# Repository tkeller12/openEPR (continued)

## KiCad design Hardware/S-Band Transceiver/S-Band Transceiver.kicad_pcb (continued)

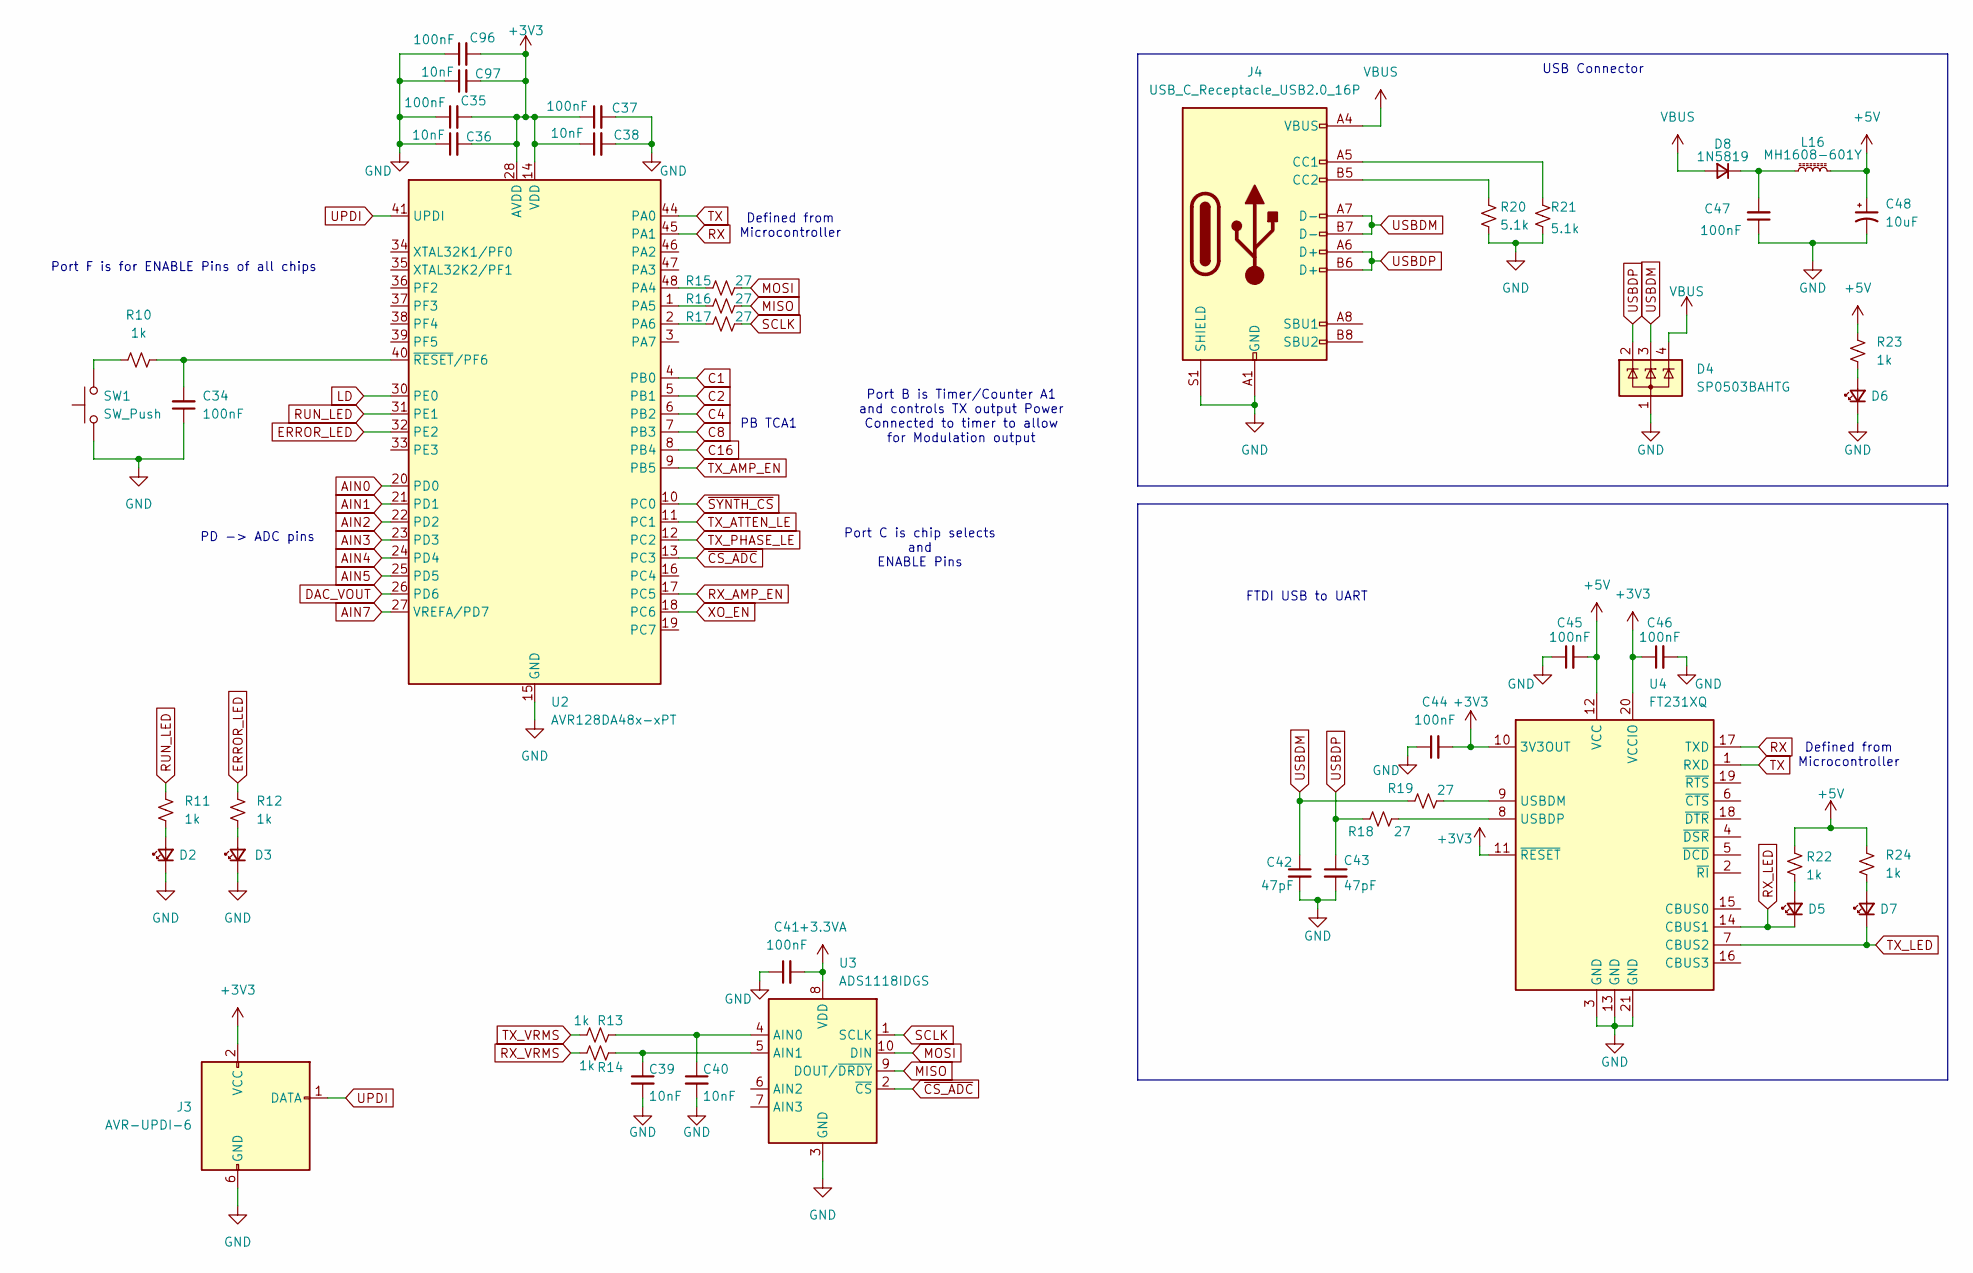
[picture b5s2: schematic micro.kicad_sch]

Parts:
C34, C35, C37, C41, C44, C45, C46, C47, C96: 100nF; C_0402_1005Metric
C36, C38, C39, C40, C97: 10nF; C_0402_1005Metric
C42, C43: 47pF; C_0402_1005Metric
C48: 10uF; CP_EIA-3216-18_Kemet-A
D2, D5, D6, D7: 150080VS75000; LED_0805_2012Metric
D3: 150080SS75000; LED_0805_2012Metric
D4: SP0503BAHTG; SOT-143; Digikey F2715CT-ND
D8: 1N5819; D_SOD-123
J3: AVR-UPDI-6; IDC-Header_2x03_P2.54mm_Vertical
J4: USB_C_Receptacle_USB2.0_16P; USB_C_Receptacle_GCT_USB4085; Digikey 2073-USB4085-GF-ACT-ND
L16: MH1608-601Y; L_0603_1608Metric
R10, R11, R12, R13, R14, R22, R23, R24: 1k; R_0603_1608Metric
R15, R16, R17, R18, R19: 27; R_0603_1608Metric
R20, R21: 5.1k; R_0603_1608Metric
SW1: SW_Push; SW_SPST_B3SL-1002P
U2: AVR128DA48x-xPT; TQFP-48_7x7mm_P0.5mm; Digikey 150-AVR128DA48-I/PT-ND
U3: ADS1118IDGS; MSOP-10_3x3mm_P0.5mm; Digikey 296-38850-1-ND
U4: FT231XQ; QFN-20-1EP_4x4mm_P0.5mm_EP2.5x2.5mm; Digikey 768-1128-1-ND

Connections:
+3.3VA: C41.2, U3.8 (VDD); also elsewhere on the board
+3V3: C35.2, C36.2, C37.1, C38.1, C44.2, C46.1, C96.2, C97.2, J3.2 (VCC), U2.14 (VDD), U2.28 (AVDD), U2.42 (VDD), U4.10 (3V3OUT), U4.11 (~RESET), U4.20 (VCCIO)
+5V: C45.2, C48.1, L16.2, R22.1, R23.1, R24.1, U4.12 (VCC); also elsewhere on the board
AIN0: U2.20 (PD0)
AIN1: U2.21 (PD1)
AIN2: U2.22 (PD2)
AIN3: U2.23 (PD3)
AIN4: U2.24 (PD4)
AIN5: U2.25 (PD5)
AIN7: U2.27 (VREFA/PD7)
C1: U2.4 (PB0); also elsewhere on the board
C2: U2.5 (PB1); also elsewhere on the board
C4: U2.6 (PB2); also elsewhere on the board
C8: U2.7 (PB3); also elsewhere on the board
C16: U2.8 (PB4); also elsewhere on the board
DAC_VOUT: U2.26 (PD6)
ERROR_LED: R12.1, U2.32 (PE2)
GND: C34.1, C35.1, C36.1, C37.2, C38.2, C39.2, C40.2, C41.1, C42.2, C43.2, C44.1, C45.1, C46.2, C47.1, C48.2, C96.1, C97.1, D2.1 (K), D3.1 (K), D4.1 (A), D6.1 (K), J3.6 (GND), J4.A1 (GND), J4.A12 (GND), J4.B1 (GND), J4.B12 (GND), J4.S1 (SHIELD), R20.2, R21.2, SW1.1, U2.15 (GND), U2.29 (GND), U2.43 (GND), U3.3 (GND), U4.3 (GND), U4.13 (GND), U4.21 (GND); also elsewhere on the board
LD: U2.30 (PE0); also elsewhere on the board
MISO: R16.2, U3.9 (DOUT/~DRDY)
MOSI: R15.2, U3.10 (DIN); also elsewhere on the board
unnamed: D2.2 (A), R11.2
unnamed: D3.2 (A), R12.2
unnamed: D5.2 (A), R22.2
unnamed: D6.2 (A), R23.2
unnamed: D7.2 (A), R24.2
unnamed: C47.2, D8.1 (K), L16.1
unnamed: J4.A5 (CC1), R21.1
unnamed: J4.B5 (CC2), R20.1
unnamed: R10.1, SW1.2
unnamed: R15.1, U2.48 (PA4)
unnamed: R16.1, U2.1 (PA5)
unnamed: R17.1, U2.2 (PA6)
unnamed: C34.2, R10.2, U2.40 (~RESET/PF6)
unnamed: C40.1, R13.2, U3.4 (AIN0)
unnamed: C39.1, R14.2, U3.5 (AIN1)
unnamed: R19.2, U4.9 (USBDM)
unnamed: R18.2, U4.8 (USBDP)
RUN_LED: R11.1, U2.31 (PE1)
RX: U2.45 (PA1), U4.17 (TXD)
RX_AMP_EN: U2.17 (PC5); also elsewhere on the board
RX_LED: D5.1 (K), U4.14 (CBUS1)
RX_VRMS: R14.1; also elsewhere on the board
SCLK: R17.2, U3.1 (SCLK); also elsewhere on the board
TX: U2.44 (PA0), U4.1 (RXD)
TX_AMP_EN: U2.9 (PB5); also elsewhere on the board
TX_ATTEN_LE: U2.11 (PC1); also elsewhere on the board
TX_LED: D7.1 (K), U4.7 (CBUS2)
TX_PHASE_LE: U2.12 (PC2); also elsewhere on the board
TX_VRMS: R13.1; also elsewhere on the board
UPDI: J3.1 (DATA), U2.41 (UPDI)
USBDM: C42.1, D4.3 (K), J4.A7 (D-), J4.B7 (D-), R19.1
USBDP: C43.1, D4.2 (K), J4.A6 (D+), J4.B6 (D+), R18.1
VBUS: D4.4 (K), D8.2 (A), J4.A4 (VBUS), J4.A9 (VBUS), J4.B4 (VBUS), J4.B9 (VBUS)
XO_EN: U2.18 (PC6); also elsewhere on the board
~CS_ADC: U2.13 (PC3), U3.2 (~CS)
~SYNTH_CS: U2.10 (PC0); also elsewhere on the board

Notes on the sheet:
Defined from Microcontroller
Port F is for ENABLE Pins of all chips
Port C is chip selects and ENABLE Pins
PB TCA1
Port B is Timer/Counter A1 and controls TX output Power Connected to timer to allow for Modulation output
PD -> ADC pins
FTDI USB to UART
USB Connector

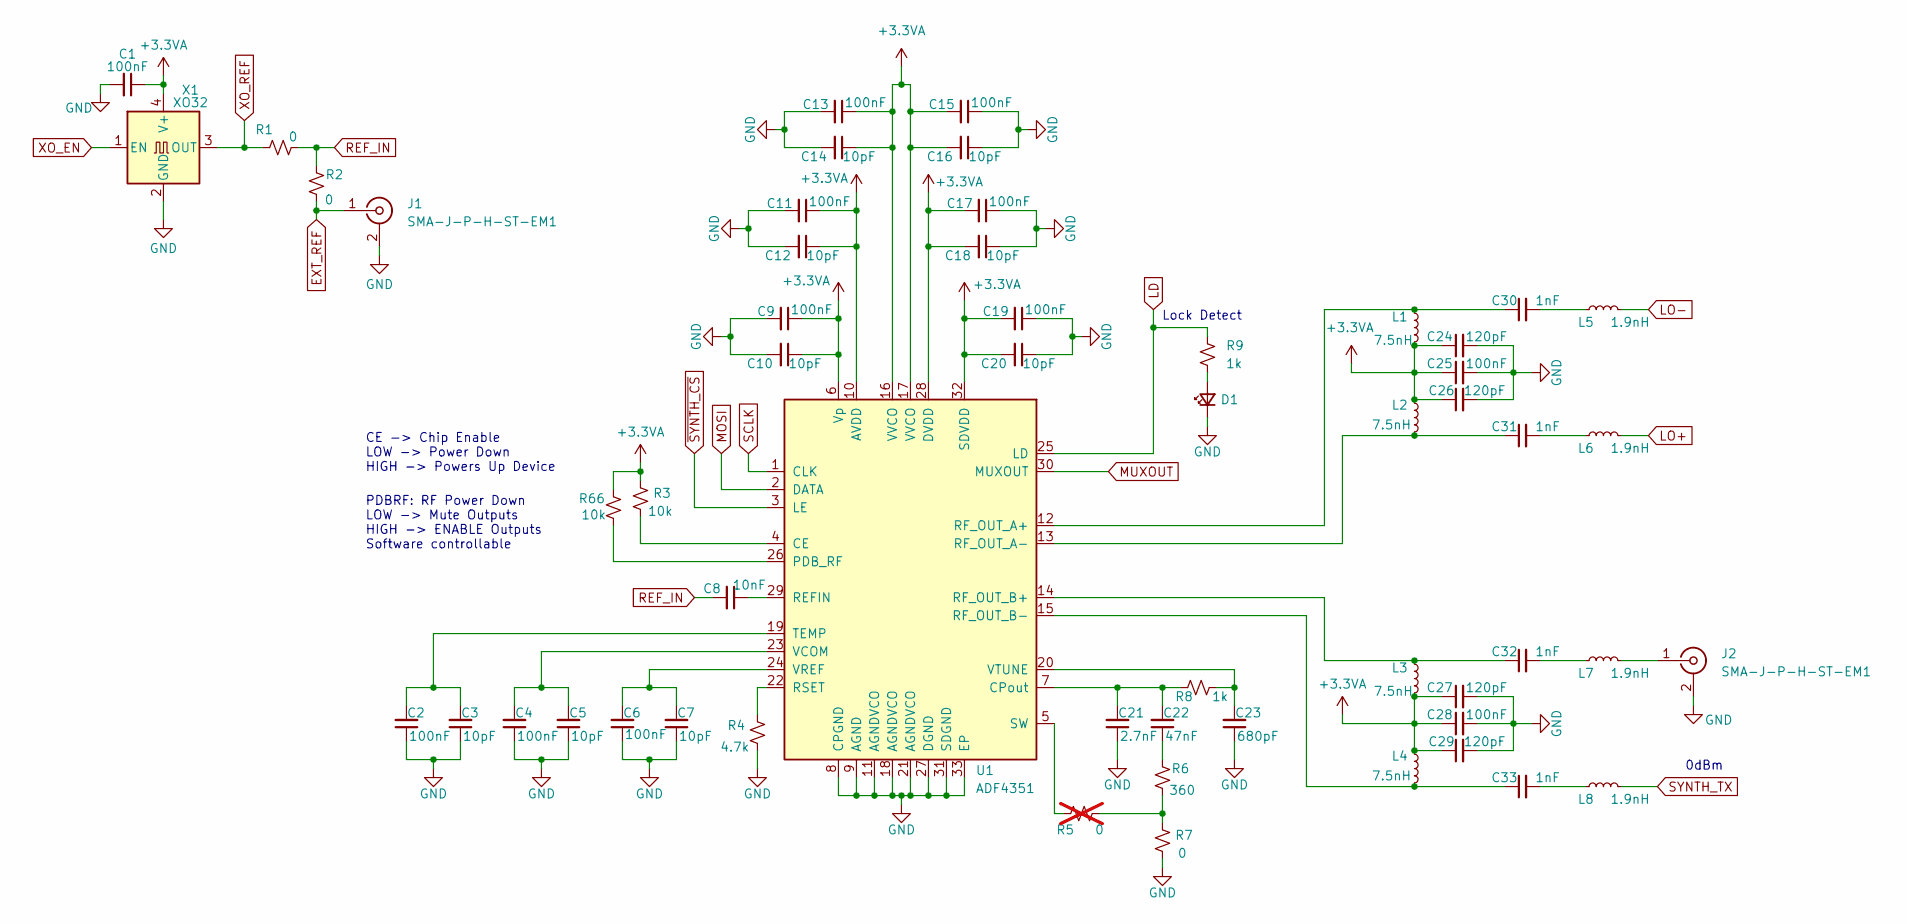
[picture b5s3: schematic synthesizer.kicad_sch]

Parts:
C1, C2, C4, C6, C9, C11, C13, C15, C17, C19, C25, C28: 100nF; C_0402_1005Metric
C3, C5, C7, C10, C12, C14, C16, C18, C20: 10pF; C_0402_1005Metric
C8: 10nF; C_0402_1005Metric
C21: 2.7nF; C_0603_1608Metric
C22: 47nF; C_0603_1608Metric
C23: 680pF; C_0603_1608Metric
C24, C26, C27, C29: 120pF; C_0402_1005Metric
C30, C31, C32, C33: 1nF; C_0402_1005Metric
D1: 150080VS75000; LED_0805_2012Metric
J1, J2: SMA-J-P-H-ST-EM1; SMA_Samtec_SMA-J-P-X-ST-EM1_EdgeMount; Digikey SAM8857-ND
L1, L2, L3, L4: 7.5nH; L_0402_1005Metric
L5, L6, L7, L8: 1.9nH; L_0402_1005Metric
R1, R2, R7: 0; R_0603_1608Metric
R3, R66: 10k; R_0603_1608Metric
R4: 4.7k; R_0603_1608Metric
R5: 0; R_0603_1608Metric; not fitted
R6: 360; R_0603_1608Metric
R8, R9: 1k; R_0603_1608Metric
U1: ADF4351; LFCSP-32-1EP_5x5mm_P0.5mm_EP3.25x3.25mm; Digikey 505-ADF4351BCPZ-RL7CT-ND
X1: XO32; Oscillator_SMD_EuroQuartz_XO32-4Pin_3.2x2.5mm

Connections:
+3.3VA: C1.1, C9.1, C10.1, C11.1, C12.1, C13.1, C14.1, C15.2, C16.2, C17.2, C18.2, C19.2, C20.2, C24.1, C25.1, C26.1, C27.1, C28.1, C29.1, L1.2, L2.1, L3.2, L4.1, R3.2, R66.1, U1.6 (Vp), U1.10 (AVDD), U1.16 (VVCO), U1.17 (VVCO), U1.28 (DVDD), U1.32 (SDVDD), X1.4 (V+); also elsewhere on the board
EXT_REF: J1.1 (In), R2.1
GND: C1.2, C2.1, C3.1, C4.1, C5.1, C6.1, C7.1, C9.2, C10.2, C11.2, C12.2, C13.2, C14.2, C15.1, C16.1, C17.1, C18.1, C19.1, C20.1, C21.1, C23.1, C24.2, C25.2, C26.2, C27.2, C28.2, C29.2, D1.1 (K), J1.2 (Ext), J2.2 (Ext), R4.2, R7.1, U1.8 (CPGND), U1.9 (AGND), U1.11 (AGNDVCO), U1.18 (AGNDVCO), U1.21 (AGNDVCO), U1.27 (DGND), U1.31 (SDGND), U1.33 (EP), X1.2 (GND); also elsewhere on the board
LD: R9.1, U1.25 (LD); also elsewhere on the board
LO+: L6.2; also elsewhere on the board
LO-: L5.2; also elsewhere on the board
MOSI: U1.2 (DATA); also elsewhere on the board
MUXOUT: U1.30 (MUXOUT)
unnamed: C22.1, R6.2
unnamed: C30.2, L5.1
unnamed: C31.2, L6.1
unnamed: C32.2, L7.1
unnamed: C33.2, L8.1
unnamed: D1.2 (A), R9.2
unnamed: J2.1 (In), L7.2
unnamed: R5.1, R6.1, R7.2
unnamed: R3.1, U1.4 (CE)
unnamed: C21.2, C22.2, R8.1, U1.7 (CPout)
unnamed: R66.2, U1.26 (PDB_RF)
unnamed: C8.1, U1.29 (REFIN)
unnamed: C30.1, L1.1, U1.12 (RF_OUT_A+)
unnamed: C31.1, L2.2, U1.13 (RF_OUT_A-)
unnamed: C32.1, L3.1, U1.14 (RF_OUT_B+)
unnamed: C33.1, L4.2, U1.15 (RF_OUT_B-)
unnamed: R4.1, U1.22 (RSET)
unnamed: R5.2, U1.5 (SW)
unnamed: C2.2, C3.2, U1.19 (TEMP)
unnamed: C4.2, C5.2, U1.23 (VCOM)
unnamed: C6.2, C7.2, U1.24 (VREF)
unnamed: C23.2, R8.2, U1.20 (VTUNE)
REF_IN: C8.2, R1.2, R2.2
SCLK: U1.1 (CLK); also elsewhere on the board
SYNTH_TX: L8.2; also elsewhere on the board
XO_EN: X1.1 (EN); also elsewhere on the board
XO_REF: R1.1, X1.3 (OUT)
~SYNTH_CS: U1.3 (LE); also elsewhere on the board

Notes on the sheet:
Lock Detect
0dBm
PDBRF: RF Power Down LOW -> Mute Outputs HIGH -> ENABLE Outputs Software controllable
CE -> Chip Enable LOW -> Power Down HIGH -> Powers Up Device

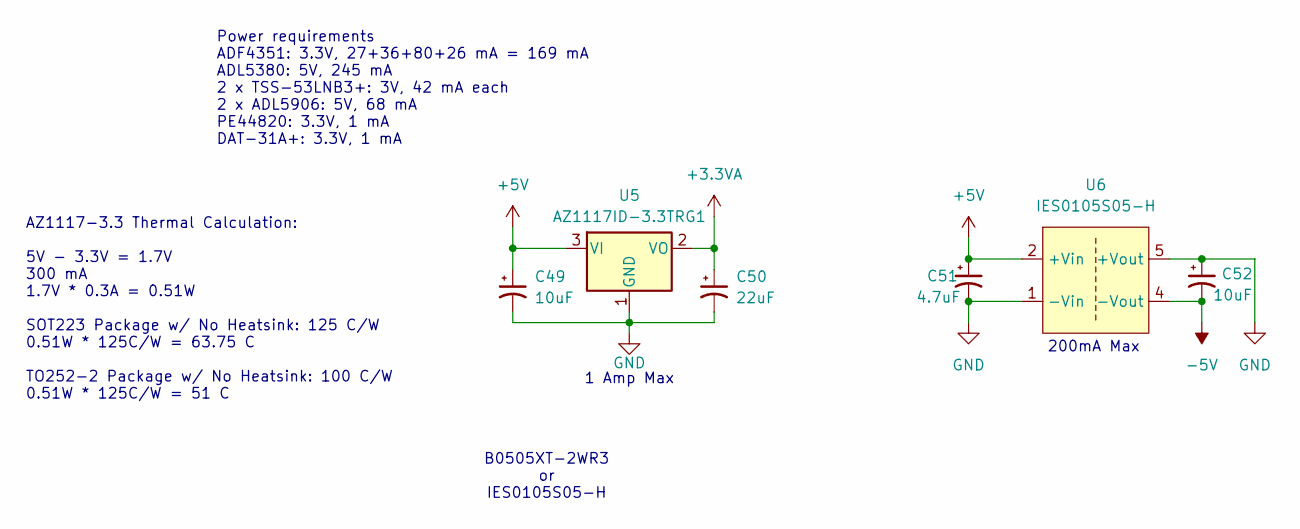
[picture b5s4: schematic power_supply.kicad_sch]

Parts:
C49, C52: 10uF
C50: 22uF
C51: 4.7uF
U5: AZ1117ID-3.3TRG1; TO-252-2; Digikey AZ1117ID-3.3TRG1-ND
U6: IES0105S05-H; Digikey 1470-IES0105S05-H-ND

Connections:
+3.3VA: C50.1, U5.2 (VO); also elsewhere on the board
+5V: C49.1, C51.1, U5.3 (VI), U6.2 (+Vin); also elsewhere on the board
-5V: C52.2, U6.4 (-Vout); also elsewhere on the board
GND: C49.2, C50.2, C51.2, C52.1, U5.1 (GND), U6.1 (-Vin), U6.5 (+Vout); also elsewhere on the board

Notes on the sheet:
B0505XT-2WR3 or IES0105S05-H
AZ1117-3.3 Thermal Calculation: 5V - 3.3V = 1.7V 300 mA 1.7V * 0.3A = 0.51W SOT223 Package w/ No Heatsink: 125 C/W 0.51W * 125C/W = 63.75 C TO252-2 Package w/ No Heatsink: 100 C/W 0.51W * 125C/W = 51 C
200mA Max
Power requirements ADF4351: 3.3V, 27+36+80+26 mA = 169 mA ADL5380: 5V, 245 mA 2 x TSS-53LNB3+: 3V, 42 mA each 2 x ADL5906: 5V, 68 mA PE44820: 3.3V, 1 mA DAT-31A+: 3.3V, 1 mA
1 Amp Max

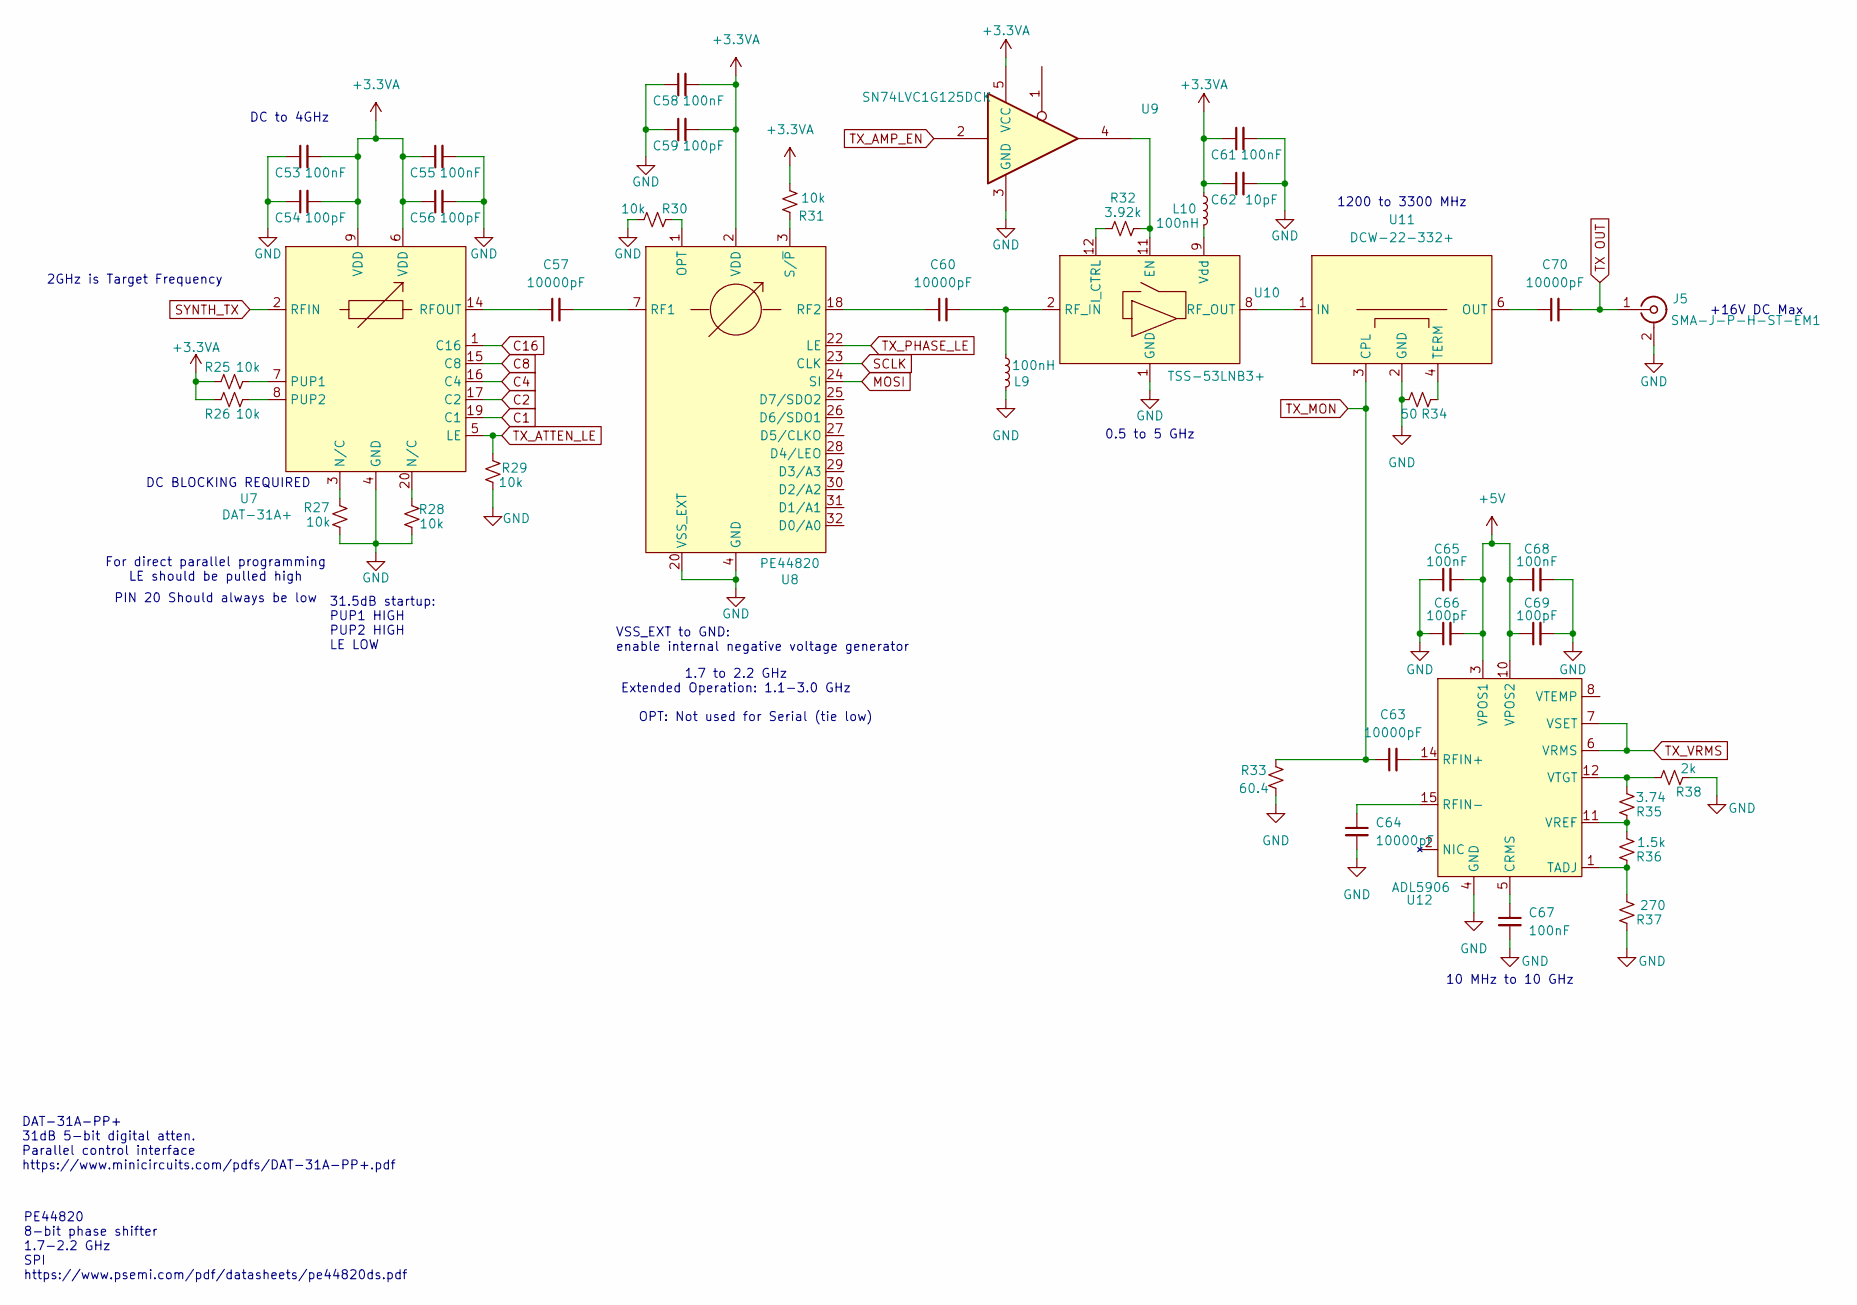
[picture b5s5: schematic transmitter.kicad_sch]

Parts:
C53, C55, C58, C61, C65, C67, C68: 100nF; C_0402_1005Metric
C54, C56, C59, C66, C69: 100pF; C_0402_1005Metric
C57, C60, C63, C64, C70: 10000pF; C_0402_1005Metric; Digikey 1284-1540-1-ND
C62: 10pF; C_0402_1005Metric
J5: SMA-J-P-H-ST-EM1; SMA_Samtec_SMA-J-P-X-ST-EM1_EdgeMount; Digikey SAM8857-ND
L9, L10: 100nH; L_0402_1005Metric
R25, R26, R27, R28, R29, R30, R31: 10k; R_0603_1608Metric
R32: 3.92k; R_0603_1608Metric
R33: 60.4; R_0603_1608Metric
R34: 50; R_0603_1608Metric
R35: 3.74; R_0603_1608Metric
R36: 1.5k; R_0603_1608Metric
R37: 270; R_0603_1608Metric
R38: 2k; R_0603_1608Metric
U7: DAT-31A+; QFN-20-1EP_4x4mm_P0.5mm_EP2.5x2.5mm; Digikey 3157-DAT-31A-PP+CT-ND
U8: PE44820; QFN-32-1EP_5x5mm_P0.5mm_EP3.6x3.6mm; Digikey 1046-1144-1-ND
U9: SN74LVC1G125DCK; SOT-23-5; Digikey 296-11604-1-ND
U10: TSS-53LNB3+; DQ1225; Digikey 3157-TSS-53LNB3+CT-ND
U11: DCW-22-332+; JC0603C; Digikey 3157-DCW-22-332+CT-ND
U12: ADL5906; QFN-16-1EP_4x4mm_P0.65mm_EP2.1x2.1mm_ThermalVias; Digikey 505-ADL5906ACPZN-R7CT-ND

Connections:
+3.3VA: C53.2, C54.2, C55.1, C56.1, C58.2, C59.2, C61.1, C62.1, L10.1, R25.2, R26.2, R31.1, U7.6 (VDD), U7.9 (VDD), U8.2 (VDD), U9.5 (VCC); also elsewhere on the board
+5V: C65.2, C66.2, C68.1, C69.1, U12.3 (VPOS1), U12.10 (VPOS2); also elsewhere on the board
C1: U7.19 (C1); also elsewhere on the board
C2: U7.17 (C2); also elsewhere on the board
C4: U7.16 (C4); also elsewhere on the board
C8: U7.15 (C8); also elsewhere on the board
C16: U7.1 (C16); also elsewhere on the board
GND: C53.1, C54.1, C55.2, C56.2, C58.1, C59.1, C61.2, C62.2, C64.2, C65.1, C66.1, C67.2, C68.2, C69.2, J5.2 (Ext), L9.2, R27.1, R28.1, R29.1, R30.1, R33.2, R34.1, R37.1, R38.2, U7.4 (GND), U7.10 (GND), U7.11 (GND), U7.12 (GND), U7.13 (GND), U7.18 (GND), U7.21 (GND), U8.4 (GND), U8.5 (GND), U8.6 (GND), U8.8 (GND), U8.9 (GND), U8.10 (GND), U8.11 (GND), U8.12 (GND), U8.13 (GND), U8.14 (GND), U8.15 (GND), U8.16 (GND), U8.17 (GND), U8.19 (GND), U8.20 (VSS_EXT), U8.21 (GND), U8.33 (PAD), U9.3 (GND), U10.1 (GND), U10.3 (GND), U10.4 (GND), U10.5 (GND), U10.6 (GND), U10.7 (GND), U10.10 (GND), U10.13 (GND), U11.2 (GND), U11.5 (GND), U12.4 (GND), U12.9 (GND), U12.17 (GND); also elsewhere on the board
MOSI: U8.24 (SI); also elsewhere on the board
unnamed: R27.2, U7.3 (N/C)
unnamed: R28.2, U7.20 (N/C)
unnamed: R25.1, U7.7 (PUP1)
unnamed: R26.1, U7.8 (PUP2)
unnamed: C57.1, U7.14 (RFOUT)
unnamed: R30.2, U8.1 (OPT)
unnamed: C57.2, U8.7 (RF1)
unnamed: C60.1, U8.18 (RF2)
unnamed: R31.2, U8.3 (S/~P)
unnamed: R32.2, U9.4, U10.11 (EN)
unnamed: R32.1, U10.12 (I_CTRL)
unnamed: C60.2, L9.1, U10.2 (RF_IN)
unnamed: U10.8 (RF_OUT), U11.1 (IN)
unnamed: L10.2, U10.9 (Vdd)
unnamed: C70.1, U11.6 (OUT)
unnamed: R34.2, U11.4 (TERM)
unnamed: C67.1, U12.5 (CRMS)
unnamed: C63.2, U12.14 (RFIN+)
unnamed: C64.1, U12.15 (RFIN-)
unnamed: R36.1, R37.2, U12.1 (TADJ)
unnamed: R35.1, R36.2, U12.11 (VREF)
unnamed: R35.2, R38.1, U12.12 (VTGT)
SCLK: U8.23 (CLK); also elsewhere on the board
SYNTH_TX: U7.2 (RFIN); also elsewhere on the board
TX OUT: C70.2, J5.1 (In)
TX_AMP_EN: U9.2; also elsewhere on the board
TX_ATTEN_LE: R29.2, U7.5 (LE); also elsewhere on the board
TX_MON: C63.1, R33.1, U11.3 (CPL)
TX_PHASE_LE: U8.22 (LE); also elsewhere on the board
TX_VRMS: U12.6 (VRMS), U12.7 (VSET); also elsewhere on the board

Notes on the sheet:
10 MHz to 10 GHz
0.5 to 5 GHz
+16V DC Max
DC to 4GHz
DC BLOCKING REQUIRED
PE44820 8-bit phase shifter 1.7-2.2 GHz SPI https://www.psemi.com/pdf/datasheets/pe44820ds.pdf
1.7 to 2.2 GHz Extended Operation: 1.1-3.0 GHz
OPT: Not used for Serial (tie low)
PIN 20 Should always be low
DAT-31A-PP+ 31dB 5-bit digital atten. Parallel control interface https://www.minicircuits.com/pdfs/DAT-31A-PP+.pdf
For direct parallel programming LE should be pulled high
1200 to 3300 MHz
31.5dB startup: PUP1 HIGH PUP2 HIGH LE LOW
2GHz is Target Frequency
VSS_EXT to GND: enable internal negative voltage generator

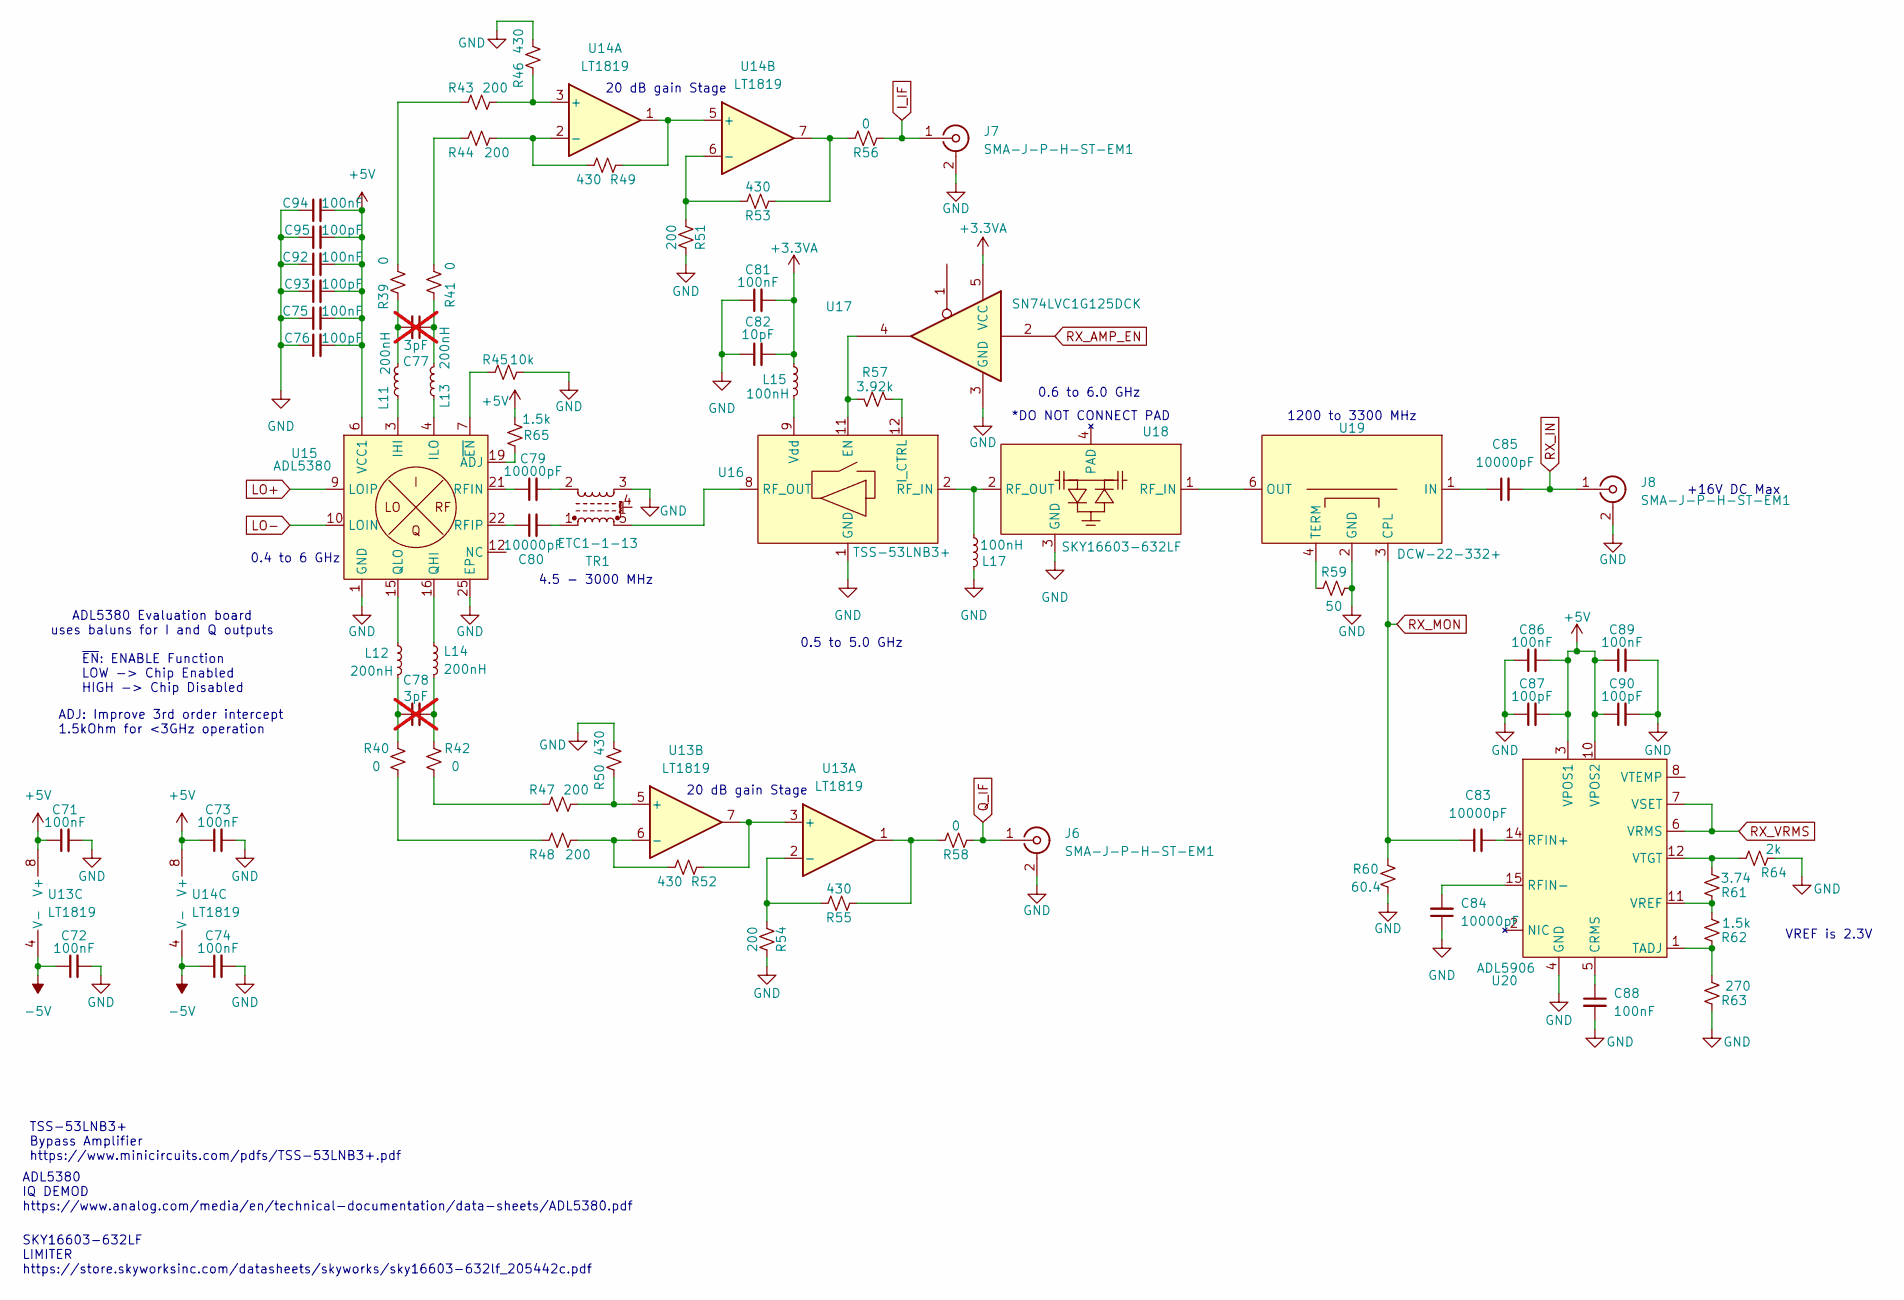
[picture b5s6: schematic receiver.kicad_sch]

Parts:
C71, C72, C73, C74, C75, C81, C86, C88, C89, C92, C94: 100nF; C_0402_1005Metric
C76, C87, C90, C93, C95: 100pF; C_0402_1005Metric
C77, C78: 3pF; C_0402_1005Metric; not fitted
C79, C80, C83, C84, C85: 10000pF; C_0402_1005Metric; Digikey 1284-1540-1-ND
C82: 10pF; C_0402_1005Metric
J6, J7, J8: SMA-J-P-H-ST-EM1; SMA_Samtec_SMA-J-P-X-ST-EM1_EdgeMount; Digikey SAM8857-ND
L11, L12, L13, L14: 200nH; L_0402_1005Metric
L15, L17: 100nH; L_0402_1005Metric
R39, R40, R41, R42, R56, R58: 0; R_0603_1608Metric
R43, R44, R47, R48, R51, R54: 200; R_0603_1608Metric
R45: 10k; R_0603_1608Metric
R46, R49, R50, R52, R53, R55: 430; R_0603_1608Metric
R57: 3.92k; R_0603_1608Metric
R59: 50; R_0603_1608Metric
R60: 60.4; R_0603_1608Metric
R61: 3.74; R_0603_1608Metric
R62, R65: 1.5k; R_0603_1608Metric
R63: 270; R_0603_1608Metric
R64: 2k; R_0603_1608Metric
TR1: ETC1-1-13; Transformer_MACOM_SM-22; Digikey 1465-1217-1-ND
U13, U14: LT1819; MSOP-8_3x3mm_P0.65mm; Digikey LT1819CS8#TRPBFCT-ND
U15: ADL5380; LFCSP-24-1EP_4x4mm_P0.5mm_EP2.3x2.3mm_ThermalVias; Digikey 505-ADL5380ACPZ-R7CT-ND
U16: TSS-53LNB3+; DQ1225; Digikey 3157-TSS-53LNB3+CT-ND
U17: SN74LVC1G125DCK; SOT-23-5; Digikey 296-11604-1-ND
U18: SKY16603-632LF; DFN-2-2.3x2.3; Digikey 863-SKY16603-632LFCT-ND
U19: DCW-22-332+; JC0603C; Digikey 3157-DCW-22-332+CT-ND
U20: ADL5906; QFN-16-1EP_4x4mm_P0.65mm_EP2.1x2.1mm_ThermalVias; Digikey 505-ADL5906ACPZN-R7CT-ND

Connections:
+3.3VA: C81.2, C82.2, L15.1, U17.5 (VCC); also elsewhere on the board
+5V: C71.1, C73.1, C75.2, C76.2, C86.2, C87.2, C89.1, C90.1, C92.2, C93.2, C94.2, C95.2, R65.1, U13.8 (V+), U14.8 (V+), U15.6 (VCC1), U15.13 (VCC2), U15.24 (VCC3), U20.3 (VPOS1), U20.10 (VPOS2); also elsewhere on the board
-5V: C72.1, C74.1, U13.4 (V-), U14.4 (V-); also elsewhere on the board
GND: C71.2, C72.2, C73.2, C74.2, C75.1, C76.1, C81.1, C82.1, C84.1, C86.1, C87.1, C88.2, C89.2, C90.2, C92.1, C93.1, C94.1, C95.1, J6.2 (Ext), J7.2 (Ext), J8.2 (Ext), L17.2, R45.1, R46.1, R50.1, R51.1, R54.1, R59.2, R60.2, R63.1, R64.2, TR1.3, U15.1 (GND), U15.2 (GND), U15.5 (GND), U15.8 (GND), U15.11 (GND), U15.14 (GND), U15.17 (GND), U15.18 (GND), U15.20 (GND), U15.23 (GND), U15.25 (EP), U16.1 (GND), U16.3 (GND), U16.4 (GND), U16.5 (GND), U16.6 (GND), U16.7 (GND), U16.10 (GND), U16.13 (GND), U17.3 (GND), U18.3 (GND), U19.2 (GND), U19.5 (GND), U20.4 (GND), U20.9 (GND), U20.17 (GND); also elsewhere on the board
I_IF: J7.1 (In), R56.2
LO+: U15.9 (LOIP); also elsewhere on the board
LO-: U15.10 (LOIN); also elsewhere on the board
unnamed: C77.1, L13.2, R41.1
unnamed: C77.2, L11.2, R39.2
unnamed: C78.1, L12.2, R40.1
unnamed: C78.2, L14.2, R42.2
unnamed: C79.2, TR1.2
unnamed: C80.2, TR1.1
unnamed: R39.1, R43.2
unnamed: R40.2, R48.2
unnamed: R41.2, R44.2
unnamed: R42.1, R47.2
unnamed: R53.2, R56.1, U14.7
unnamed: R55.2, R58.1, U13.1
unnamed: R52.2, U13.3 (+), U13.7
unnamed: R54.2, R55.1, U13.2 (-)
unnamed: R47.1, R50.2, U13.5 (+)
unnamed: R48.1, R52.1, U13.6 (-)
unnamed: R43.1, R46.2, U14.3 (+)
unnamed: R44.1, R49.1, U14.2 (-)
unnamed: R49.2, U14.1, U14.5 (+)
unnamed: R51.2, R53.1, U14.6 (-)
unnamed: R65.2, U15.19 (ADJ)
unnamed: L11.1, U15.3 (IHI)
unnamed: L13.1, U15.4 (ILO)
unnamed: L14.1, U15.16 (QHI)
unnamed: L12.1, U15.15 (QLO)
unnamed: C79.1, U15.21 (RFIN)
unnamed: C80.1, U15.22 (RFIP)
unnamed: R45.2, U15.7 (~EN)
unnamed: R57.2, U16.11 (EN), U17.4
unnamed: R57.1, U16.12 (I_CTRL)
unnamed: L17.1, U16.2 (RF_IN), U18.2 (RF_OUT)
unnamed: TR1.5, U16.8 (RF_OUT)
unnamed: L15.2, U16.9 (Vdd)
unnamed: U18.1 (RF_IN), U19.6 (OUT)
unnamed: C85.1, U19.1 (IN)
unnamed: R59.1, U19.4 (TERM)
unnamed: C88.1, U20.5 (CRMS)
unnamed: C83.2, U20.14 (RFIN+)
unnamed: C84.2, U20.15 (RFIN-)
unnamed: R62.1, R63.2, U20.1 (TADJ)
unnamed: R61.1, R62.2, U20.11 (VREF)
unnamed: R61.2, R64.1, U20.12 (VTGT)
Q_IF: J6.1 (In), R58.2
RX_AMP_EN: U17.2; also elsewhere on the board
RX_IN: C85.2, J8.1 (In)
RX_MON: C83.1, R60.1, U19.3 (CPL)
RX_VRMS: U20.6 (VRMS), U20.7 (VSET); also elsewhere on the board

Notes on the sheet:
4.5 - 3000 MHz
TSS-53LNB3+ Bypass Amplifier https://www.minicircuits.com/pdfs/TSS-53LNB3+.pdf
0.4 to 6 GHz
20 dB gain Stage
~{EN}: ENABLE Function LOW -> Chip Enabled HIGH -> Chip Disabled
0.6 to 6.0 GHz
*DO NOT CONNECT PAD
ADL5380 IQ DEMOD https://www.analog.com/media/en/technical-documentation/data-sheets/ADL5380.pdf
SKY16603-632LF LIMITER https://store.skyworksinc.com/datasheets/skyworks/sky16603-632lf_205442c.pdf
+16V DC Max
VREF is 2.3V
1200 to 3300 MHz
ADL5380 Evaluation board uses baluns for I and Q outputs
0.5 to 5.0 GHz
ADJ: Improve 3rd order intercept 1.5kOhm for <3GHz operation
